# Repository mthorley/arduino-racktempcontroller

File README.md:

# Arduino Rack Temperature Controller

To temperature control and monitor a small (12U) network rack system using PWM fans and thermometers managed using an Arduino Mega with a custom designed shield:

Above rack has:
- 4 fans mounted (2 top and 2 base) in the rack
- 2 temperature sensors one at the top and base
- [Modular 3d printed model](https://github.com/mthorley/2u-rack-3dprint-model) 2U rack housing Arduino temperature controller and OLED shown far left

# Features and Specification
* Uses [Freetronics EtherMega](https://www.freetronics.com.au/collections/arduino/products/ethermega-arduino-mega-2560-compatible-with-onboard-ethernet#.XXMqnZMzY0o) Arduino board although likely any Mega board can reuse the shield
* Shield outline derived from Jonathan Oxer's [ProtoShieldMega](https://github.com/freetronics/ProtoShieldMega)
* Power over Ethernet 802.3af support using [Freetronics PoE module](https://www.freetronics.com.au/products/power-over-ethernet-regulator-8023af) to power the board (and reset it), thermometers, fans and display to simplify power and wire management
* Measures temperatures using [DS18B20](https://makeradvisor.com/tools/ds18b20-digital-temperature-sensor/) housed in metal cable assembly with an accuracy of +/- 0.5&deg;C
* Uses [Freetronics OLED](https://www.freetronics.com.au/pages/oled128-quickstart-guide) via SPI to display the temperature and fan states of the rack
* Works with PWM fans of either 5 or 12V and supports configurable frequency (default 25kHz)
* Uses an [passive infrared sensor](https://www.keyestudio.com/2016-new-keyestudio-pir-motion-sensor-for-arduino-p0488-p0488.html) to prevent burn in for OLED display, only enabling the display on a PIR trigger
* Monitors and displays fan tachometer output to verify RPM is within expected range and fan has not stalled
* Publishes all fan, temperature, error states and logs to an MQTT endpoint and topics for analysis and visualisation
* Software must support any number of temperature devices and fans to enable testing and reuse

# Initial Design
Initial design was based on a separate (non-shield) board using a [MAX31790](https://www.maximintegrated.com/en/products/sensors/MAX31790.html) for fan PWM control and tach measurement integrated with an Arduino Uno using I<sup>2</sup>C. However due to Uno memory limitations of <32k, I upgraded to the Mega with 256k. Code is however included under [MAX31790FanControl.cpp](src/MAX31790FanControl.cpp).

Using a Mega also enabled the PWM control and tach measurement to be done by the Mega pinout and all in software simplifying the overall hardware solution.

# Shield Design
The shield design outline is based on [ProtoShieldMega](https://github.com/freetronics/ProtoShieldMega). The top side of the PCB layout is illustrated. The schematic and PCB design files are under [Eagle](/Eagle). EAGLE PCB design software is available from https://www.autodesk.com/products/eagle/free-download and is free for non-commercial use.

## Pin Mapping
| Pin | Mapping |
|-----|---------|
|2, 4, 7| OLED DC, Reset, CS |
|8      | Onewire DS for thermos |
| 11, 12, 5, 3 | Fan PWM 1-4 |
| 18, 19, 20, 21 | Fan Tach 1-4 for RPM interrupts |
| 6 | IR sensor |

## Schematic

## PCB

## Manufacture
I used [DirtyPCBs](https://dirtypcbs.com/store/pcbs) to manufacture the boards. They also support [design rules checking and CAM Gerber export](https://dirtypcbs.com/store/pcbs/about#cam) for EAGLE, which ensures the PCB layout conforms to their manufacture processes and the Gerber files produced will pass.

I then soldered (or used solder paste for surface mount) the parts in place. For the surface mount work, I used a heat gun and roughly followed the [heat profile](http://www.chemtools.com.au/download/technical-and-safety-data-sheets/solders-pastes-and-fluxes/SAC305CR318%20SAC305%20Solder%20Paste/SAC305CR318%20TDS.pdf) by modifying the gun temperature manually. [YouTube videos](https://www.youtube.com/watch?v=W0BhGieg4II) explain how to do this. 

## Shield Mounted
The shield mounted with the EtherMega.

Minor error on the power circuit which required a track cut and wire from VIN to Fan power. This has been corrected on the Eagle files.

# Display
OLED display to render fan and temperature states showing the fan temperatures in the top row, and the fan RPMs as a percentage of maximum RPM in the lower rows. The fan RPM % does not always accurately map to the input PWM duty cycle - the [fans](https://noctua.at/en/nf-s12b-redux-1200-pwm/specification) I am using have a +/- 10% variance on RPM. The display also supports 90 degree rotation to support rack mounting.

## Font Generation for OLED
Generated new fonts using [GLDCFontCreator](https://github.com/freetronics/FTOLED/wiki/Displaying-Text#defining-new-fonts).

## MQTT Dashboard
I used the mobile app [IoT MQTT Panel](https://play.google.com/store/apps/details?id=snr.lab.iotmqttpanel.prod&hl=en) to render the MQTT topics which supports configurable panels per topic and different rendering options:

# Code 
Development done using [PlatformIO](https://platformio.org/) which supports multiple boards and library management.  

## Explanation
The main routine loop executes the [RackTempController](src/RackTempController.cpp) process method below which reads the temperature sensors, adjusts the fan speed based on the temperatures, reads and verifies the fan speed RPM is as requested by the PWM dutycycle within a tolerance and analyses temperature trends using a moving average.

```c++ 
void RackTempController::process(RackState_t& rs) {
    
    // read temperatures
    readTempStates(rs.thermos);

    // adjust fan speeds based on temps
    adjustFanSpeeds(rs);
    
    // read fan tach/rpms - delay of 750ms per fan
    readFanSpeeds(rs.fans);

    // verify fan PWMs matches RPMs
    verifyFanStates(rs.fans);

    // analyse trends
    analyseTrends(rs);
};
```
Thermos and fan configuration is created via [RackTempController::build()](src/RackTempController.cpp#L219) which enables any number of thermos or fans to be used. The OLED display class however, is fixed to the specification above.

## Dependent Libraries

All libraries were loaded and managed used PlatformIO's library management. 

| Library | Purpose |
|---------|---------|
| DallasTemperature | Measures temperature of DS18* devices using OneWire |
| FTOLED  | Graphics library to drive OLED |
| SD      | Dependency for FTOLED - not used |
| Ethernet | Ethernet, DHCP support |
| ArduinoMqttClient | MQTT client |
| TimerOne | PWM control for Timer1 |
| TimerThree | PWM control for Timer3 |
| ArduinoLog | Logging framework |
| ArduinoSTL | STL library used for map, vector etc |

## Rack Mount

Further details on the rack mount design: [3D printed model](https://github.com/mthorley/2u-rack-3dprint-model).

# TODO
- Update this README!
- Create a config endpoint - possibly via MQTT subscribe to enable changes to MQTT params, temp threshold etc. 
- Improve MQTT events
- Watchdog via AWS lambda which reboots via PoE
- Look at FreeRTOS or [Helios](https://github.com/MannyPeterson/HeliOS) and work out if its worth it
- Make it cheaper

# Credits
First and foremost to [Jonathan Oxer](https://www.patreon.com/superhouse).

Secondly all the excellent library contributors used in the project.

# License
Hardware design licensed under the TAPR Open Hardware License (www.tapr.org/OHL) and GNU. The [license](Eagle/license) folder within this repository also contains a copy of this license in plain text format.

Software licensed under GPLv3 - see [license.md](license.md) file for details.

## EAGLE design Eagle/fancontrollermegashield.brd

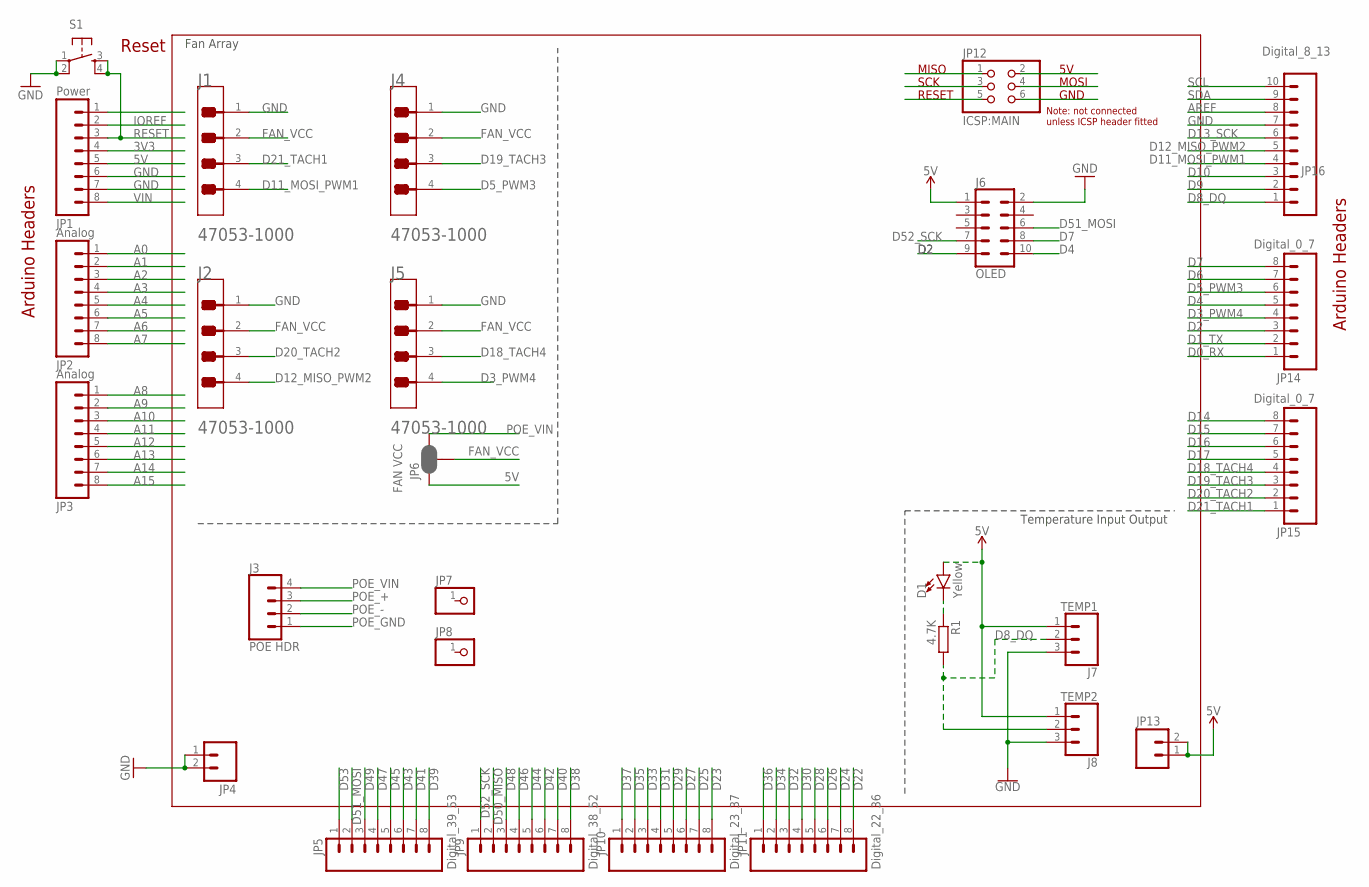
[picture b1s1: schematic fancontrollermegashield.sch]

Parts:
D1: Yellow; LED-0603
J1: FAN1; MOLEX_47053-1000_0
J2, J4, J5: MOLEX_47053-1000MOLEX_47053-1000_0_0; MOLEX_47053-1000_0
J3: POE HDR; 1X04
J6: OLED; 2X5-SHROUDED
J7: TEMP1; MOLEX-1X3
J8: TEMP2; MOLEX-1X3
JP1: Power; 1X08
JP2, JP3: Analog; 1X08
JP4, JP13: M02PTH; 1X02
JP5: Digital_39_53; 1X08
JP6: FAN VCC; SMT-JUMPER_3_2-NC_PASTE_SILK
JP7, JP8: PINHD-1X1; 1X01
JP9: Digital_38_52; 1X08
JP10: Digital_23_37; 1X08
JP11: Digital_22_36; 1X08
JP12: ICSP:MAIN; 2X03
JP14, JP15: Digital_0_7; 1X08
JP16: Digital_8_13; 1X10
R1: 4.7K; R0603
S1: TAC_SWITCHPTH; TACTILE-PTH

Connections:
3V3: JP1.4
5V: D1.A, J6.1, J7.1, J8.1, JP1.5, JP6.1, JP13.1, JP13.2
A0: JP2.1
A1: JP2.2
A2: JP2.3
A3: JP2.4
A4: JP2.5
A5: JP2.6
A6: JP2.7
A7: JP2.8
A8: JP3.1
A9: JP3.2
A10: JP3.3
A11: JP3.4
A12: JP3.5
A13: JP3.6
A14: JP3.7
A15: JP3.8
AREF: JP16.8
D0_RX: JP14.1
D1_TX: JP14.2
D2: J6.9, JP14.3
D3_PWM4: J5.4, JP14.4
D4: J6.10, JP14.5
D5_PWM3: J4.4, JP14.6
D6: JP14.7
D7: J6.8, JP14.8
D8_DQ: J7.2, J8.2, JP16.1, R1.2
D9: JP16.2
D10: JP16.3
D11_MOSI_PWM1: J1.4, JP16.4
D12_MISO_PWM2: J2.4, JP16.5
D13_SCK: JP16.6
D14: JP15.8
D15: JP15.7
D16: JP15.6
D17: JP15.5
D18_TACH4: J5.3, JP15.4
D19_TACH3: J4.3, JP15.3
D20_TACH2: J2.3, JP15.2
D21_TACH1: J1.3, JP15.1
D22: JP11.8
D23: JP10.8
D24: JP11.7
D25: JP10.7
D26: JP11.6
D27: JP10.6
D28: JP11.5
D29: JP10.5
D30: JP11.4
D31: JP10.4
D32: JP11.3
D33: JP10.3
D34: JP11.2
D35: JP10.2
D36: JP11.1
D37: JP10.1
D38: JP9.8
D39: JP5.8
D40: JP9.7
D41: JP5.7
D42: JP9.6
D43: JP5.6
D44: JP9.5
D45: JP5.5
D46: JP9.4
D47: JP5.4
D48: JP9.3
D49: JP5.3
D50_MISO: JP9.2
D51_MOSI: J6.6, JP5.2
D52_SCK: J6.7, JP9.1
D53: JP5.1
FAN_VCC: J1.2, J2.2, J4.2, J5.2, JP6.2
GND: J1.1, J2.1, J4.1, J5.1, J6.2, J7.3, J8.3, JP1.6, JP1.7, JP4.1, JP4.2, JP16.7, S1.1, S1.2
IOREF: JP1.2
unnamed: D1.C, R1.1
POE_+: J3.3
POE_-: J3.2
POE_GND: J3.1
POE_VIN: J3.4, JP6.3
RESET: JP1.3, S1.3, S1.4
SCL: JP16.10
SDA: JP16.9
VIN: JP1.8

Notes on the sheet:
Arduino Headers
Reset
GND
MISO
RESET
SCK
MOSI
Note: not connected unless ICSP header fitted
Temperature Input Output
Fan Array

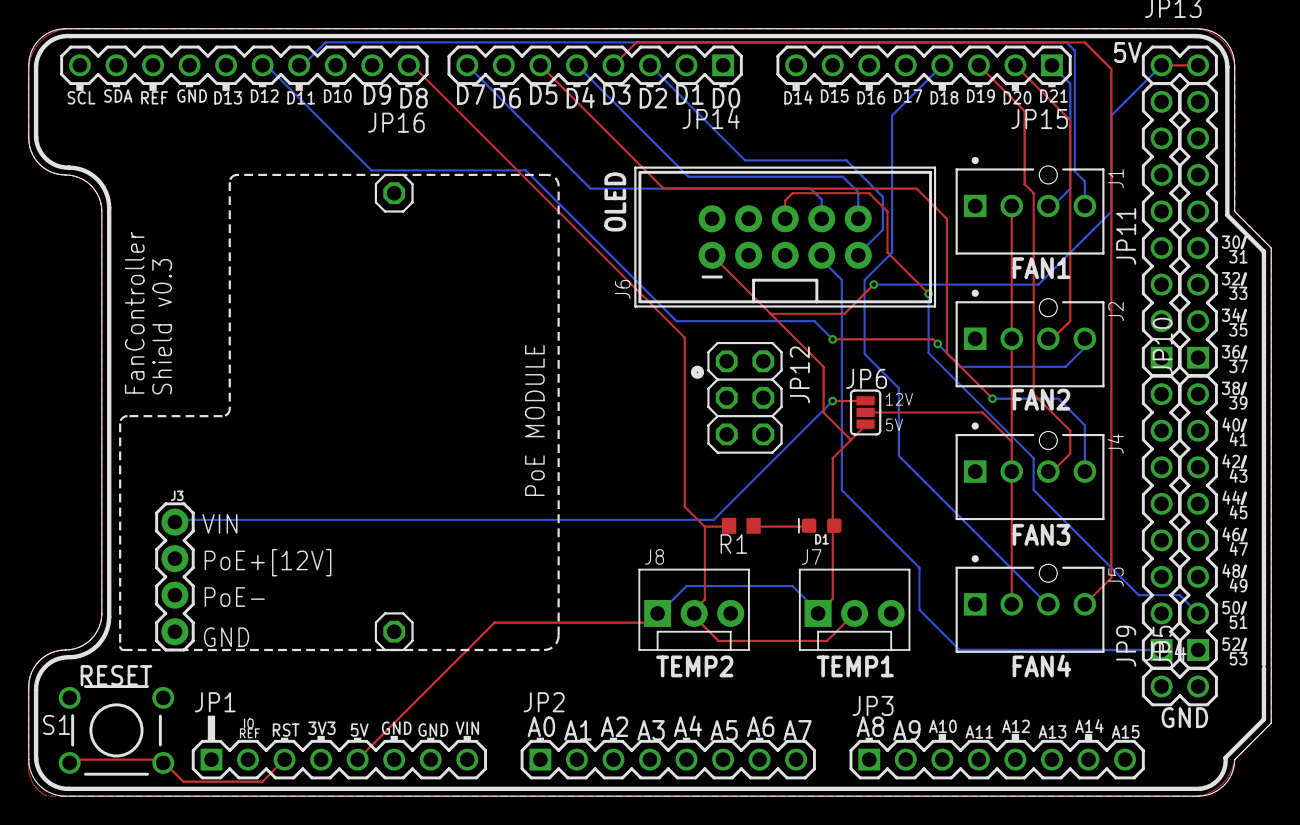
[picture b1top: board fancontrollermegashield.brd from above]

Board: 2 copper layers, 86.4 x 53.3 mm, 27 parts (0 on the bottom side), 20 nets.

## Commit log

2019-09-20 Initial
2019-09-20 Cleanup
2019-09-21 Eagle files
2019-09-21 Minor corrections
2019-09-26 Updated logging, better method descriptions
2019-09-26 Cleaned up tach versus rpm
2019-09-26 Fix up fan tach error
2019-09-26 Wiki images
2019-09-28 Fixed RPM variance issue
2019-10-04 Create LICENSE
2019-10-04 License
2020-01-27 Added temp threshold to trigger 100% PWM
2020-01-27 Layout
2020-08-10 Return MQTT error on initialise
2020-08-10 Support 90 rotation for rack mount
2020-08-10 Display rotation note
2020-08-16 Enabled MQTT subscribe callback to switch OLED on/off
2020-08-16 Reference 2U rack 3d model repo
2021-01-31 Control of display via device/config topic callback
2021-03-01 Whitespace
2021-05-15 Documentation updates

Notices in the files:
parts and their libraries:
SparkFun-Connectors: Licensing: Creative Commons ShareAlike 4.0 International - https://creativecommons.org/licenses/by-sa/4.0
